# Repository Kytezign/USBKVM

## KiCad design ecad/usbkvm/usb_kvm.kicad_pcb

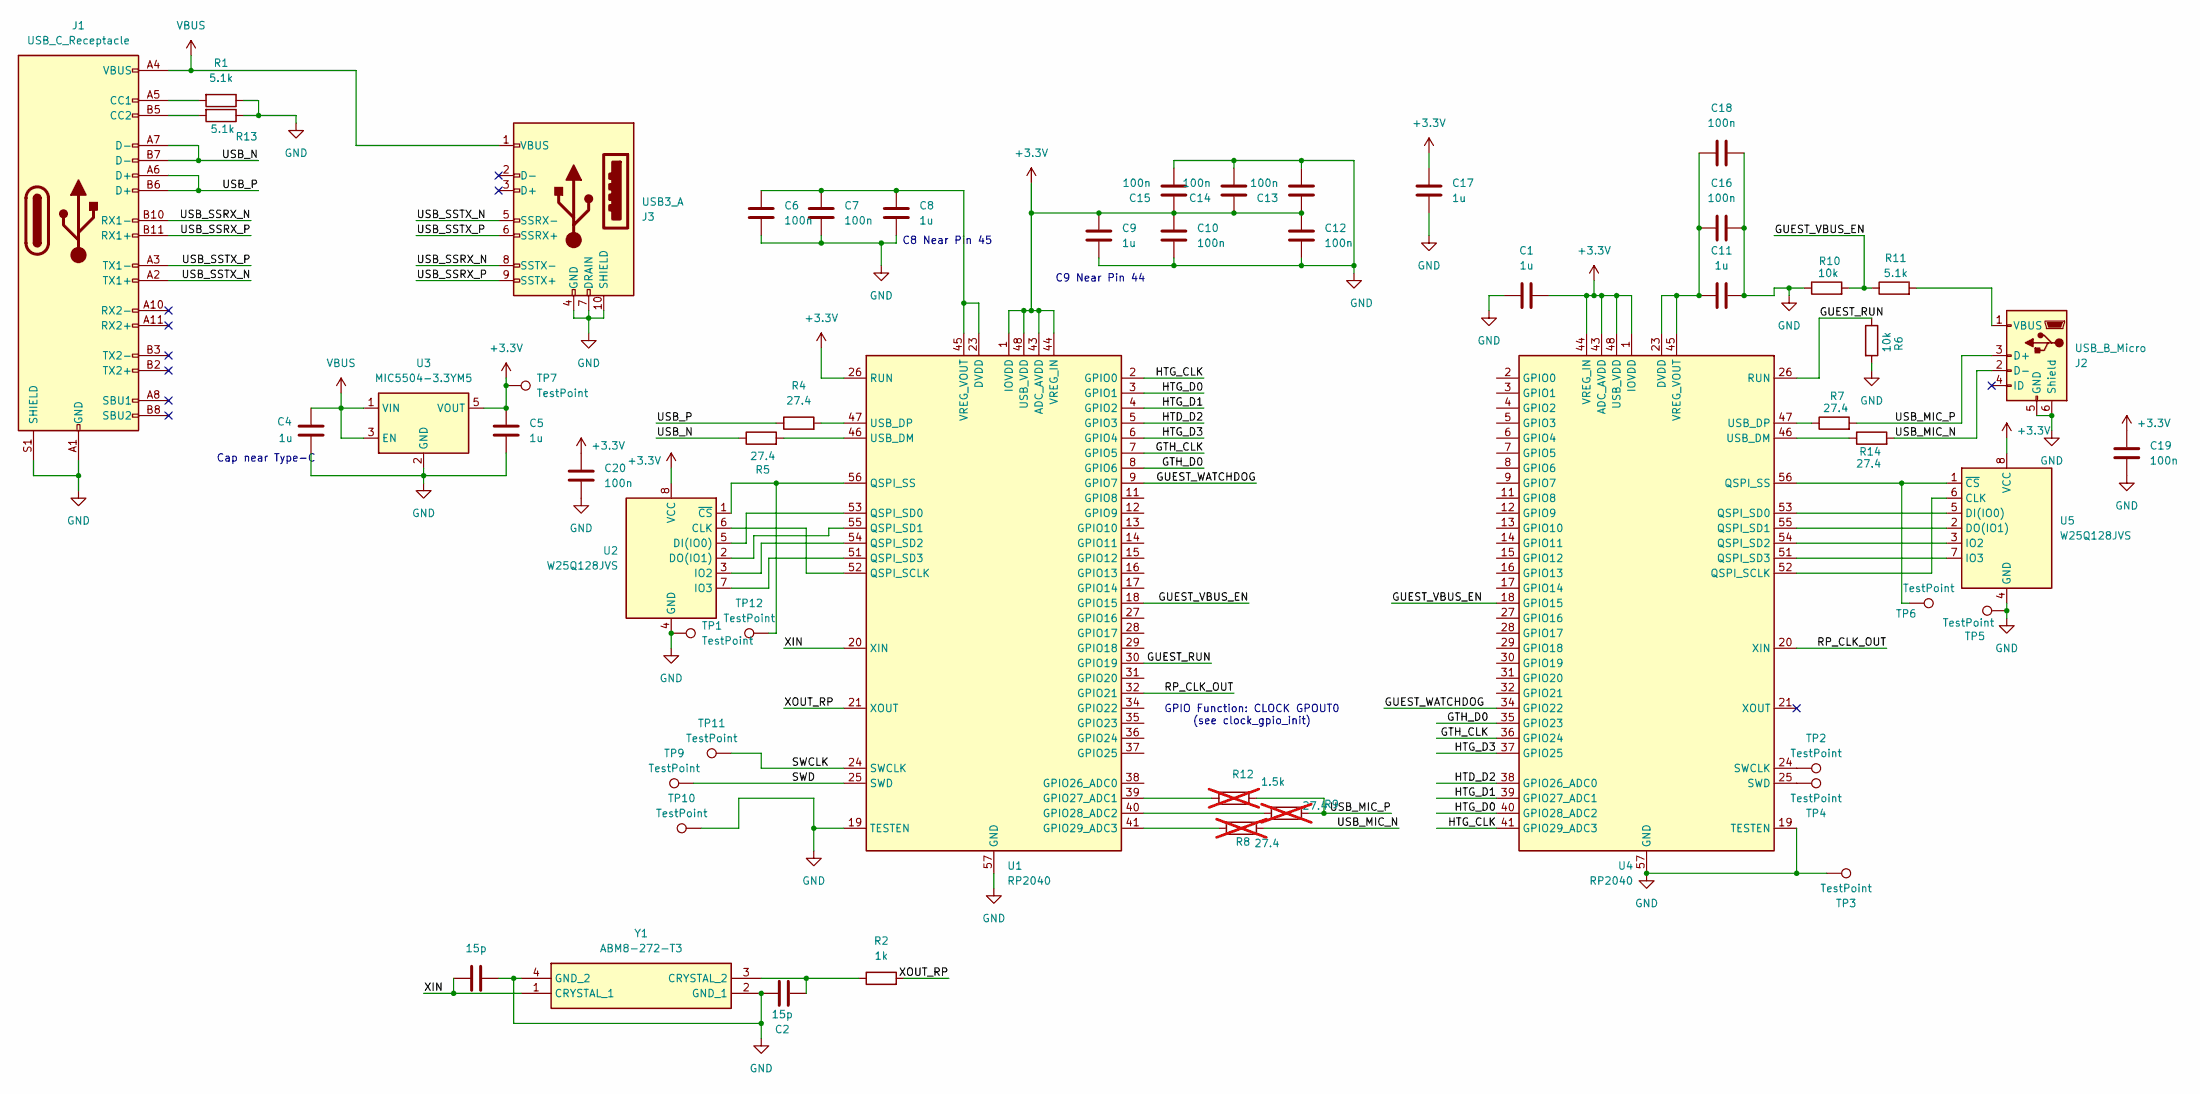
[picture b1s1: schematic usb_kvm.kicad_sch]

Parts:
C1, C4, C5, C8, C9, C11, C17: 1u; C_0402_1005Metric_Pad0.74x0.62mm_HandSolder
C2, C3: 15p; C_0402_1005Metric_Pad0.74x0.62mm_HandSolder
C6, C7, C10, C12, C13, C14, C15, C16, C18, C19, C20: 100n; C_0402_1005Metric_Pad0.74x0.62mm_HandSolder
J1: USB_C_Receptacle; USB405603A
J2: USB_B_Micro; 101181920001LF
J3: USB3_A; USBA3SRA
R1, R11, R13: 5.1k; R_0402_1005Metric_Pad0.72x0.64mm_HandSolder
R2: 1k; R_0402_1005Metric_Pad0.72x0.64mm_HandSolder
R4, R5, R7, R14: 27.4; R_0402_1005Metric_Pad0.72x0.64mm_HandSolder
R6, R10: 10k; R_0402_1005Metric_Pad0.72x0.64mm_HandSolder
R8, R9: 27.4; R_0402_1005Metric_Pad0.72x0.64mm_HandSolder; not fitted
R12: 1.5k; R_0402_1005Metric_Pad0.72x0.64mm_HandSolder; not fitted
TP1, TP5, TP6, TP7, TP12: TestPoint; TestPoint_THTPad_D1.0mm_Drill0.5mm
TP2, TP3, TP4, TP9, TP10, TP11: TestPoint; TestPoint_Pad_1.5x1.5mm
U1, U4: RP2040; QFN-56-1EP_7x7mm_P0.4mm_EP3.2x3.2mm
U2, U5: W25Q128JVS; SOIC-8_5.23x5.23mm_P1.27mm
U3: MIC5504-3.3YM5; SOT-23-5
Y1: ABM8-272-T3; ABM8272T3; Mouser Part Number 815-ABM8-272-T3

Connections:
+3.3V: C1.2, C5.1, C9.1, C10.1, C12.1, C13.1, C14.1, C15.1, C17.1, C19.1, C20.1, TP7.1, U1.1 (IOVDD), U1.10 (IOVDD), U1.22 (IOVDD), U1.26 (RUN), U1.33 (IOVDD), U1.42 (IOVDD), U1.43 (ADC_AVDD), U1.44 (VREG_IN), U1.48 (USB_VDD), U1.49 (IOVDD), U2.8 (VCC), U3.5 (VOUT), U4.1 (IOVDD), U4.10 (IOVDD), U4.22 (IOVDD), U4.33 (IOVDD), U4.42 (IOVDD), U4.43 (ADC_AVDD), U4.44 (VREG_IN), U4.48 (USB_VDD), U4.49 (IOVDD), U5.8 (VCC)
/GTH_CLK: U1.7 (GPIO5), U4.36 (GPIO24)
/GTH_D0: U1.8 (GPIO6), U4.35 (GPIO23)
/GUEST_RUN: R6.1, U1.30 (GPIO19), U4.26 (RUN)
/GUEST_VBUS_EN: R10.2, R11.1, U1.18 (GPIO15), U4.18 (GPIO15)
/GUEST_WATCHDOG: U1.9 (GPIO7), U4.34 (GPIO22)
/HTD_D2: U1.5 (GPIO3), U4.38 (GPIO26_ADC0)
/HTG_CLK: U1.2 (GPIO0), U4.41 (GPIO29_ADC3)
/HTG_D0: U1.3 (GPIO1), U4.40 (GPIO28_ADC2)
/HTG_D1: U1.4 (GPIO2), U4.39 (GPIO27_ADC1)
/HTG_D3: U1.6 (GPIO4), U4.37 (GPIO25)
/RP_CLK_OUT: U1.32 (GPIO21), U4.20 (XIN)
/SWCLK: TP11.1, U1.24 (SWCLK)
/SWD: TP9.1, U1.25 (SWD)
/USB_MIC_N: J2.2 (D-), R8.1, R14.2
/USB_MIC_P: J2.3 (D+), R7.2, R9.2, R12.2
/USB_N: J1.A7 (D-), J1.B7 (D-), R5.1
/USB_P: J1.A6 (D+), J1.B6 (D+), R4.1
/USB_SSRX_N: J1.B10 (RX1-), J3.8 (SSTX-)
/USB_SSRX_P: J1.B11 (RX1+), J3.9 (SSTX+)
/USB_SSTX_N: J1.A2 (TX1+), J3.5 (SSRX-)
/USB_SSTX_P: J1.A3 (TX1-), J3.6 (SSRX+)
/XIN: C3.1, U1.20 (XIN), Y1.1 (CRYSTAL_1)
/XOUT_RP: R2.2, U1.21 (XOUT)
GND: C1.1, C2.1, C3.2, C4.2, C5.2, C6.2, C7.2, C8.2, C9.2, C10.2, C11.2, C12.2, C13.2, C14.2, C15.2, C16.2, C17.2, C18.2, C19.2, C20.2, J1.A1 (GND), J1.A12 (GND), J1.B1 (GND), J1.B12 (GND), J1.MH3, J1.S1 (SHIELD), J2.5 (GND), J2.6 (Shield), J3.4 (GND), J3.7 (DRAIN), J3.10 (SHIELD), R1.1, R6.2, R10.1, R13.1, TP1.1, TP3.1, TP5.1, TP10.1, U1.19 (TESTEN), U1.57 (GND), U2.4 (GND), U3.2 (GND), U4.19 (TESTEN), U4.57 (GND), U5.4 (GND), Y1.2 (GND_1), Y1.4 (GND_2)
unnamed: J1.A5 (CC1), R1.2
unnamed: J1.B5 (CC2), R13.2
unnamed: J2.1 (VBUS), R11.2
unnamed: R12.1, U1.39 (GPIO27_ADC1)
unnamed: R9.1, U1.40 (GPIO28_ADC2)
unnamed: R8.2, U1.41 (GPIO29_ADC3)
unnamed: U1.52 (QSPI_SCLK), U2.6 (CLK)
unnamed: U1.53 (QSPI_SD0), U2.5 (DI(IO0))
unnamed: U1.55 (QSPI_SD1), U2.2 (DO(IO1))
unnamed: U1.54 (QSPI_SD2), U2.3 (IO2)
unnamed: U1.51 (QSPI_SD3), U2.7 (IO3)
unnamed: TP12.1, U1.56 (QSPI_SS), U2.1 (~CS)
unnamed: R5.2, U1.46 (USB_DM)
unnamed: R4.2, U1.47 (USB_DP)
unnamed: C6.1, C7.1, C8.1, U1.23 (DVDD), U1.45 (VREG_VOUT), U1.50 (DVDD)
unnamed: U4.52 (QSPI_SCLK), U5.6 (CLK)
unnamed: U4.53 (QSPI_SD0), U5.5 (DI(IO0))
unnamed: U4.55 (QSPI_SD1), U5.2 (DO(IO1))
unnamed: U4.54 (QSPI_SD2), U5.3 (IO2)
unnamed: U4.51 (QSPI_SD3), U5.7 (IO3)
unnamed: TP6.1, U4.56 (QSPI_SS), U5.1 (~CS)
unnamed: TP2.1, U4.24 (SWCLK)
unnamed: TP4.1, U4.25 (SWD)
unnamed: R14.1, U4.46 (USB_DM)
unnamed: R7.1, U4.47 (USB_DP)
unnamed: C11.1, C16.1, C18.1, U4.23 (DVDD), U4.45 (VREG_VOUT), U4.50 (DVDD)
unnamed: C2.2, R2.1, Y1.3 (CRYSTAL_2)
VBUS: C4.1, J1.A4 (VBUS), J1.A9 (VBUS), J1.B4 (VBUS), J1.B9 (VBUS), J3.1 (VBUS), U3.1 (VIN), U3.3 (EN)

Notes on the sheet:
C9 Near Pin 44
GPIO Function: CLOCK GPOUT0 (see clock_gpio_init)
Cap near Type-C
C8 Near Pin 45

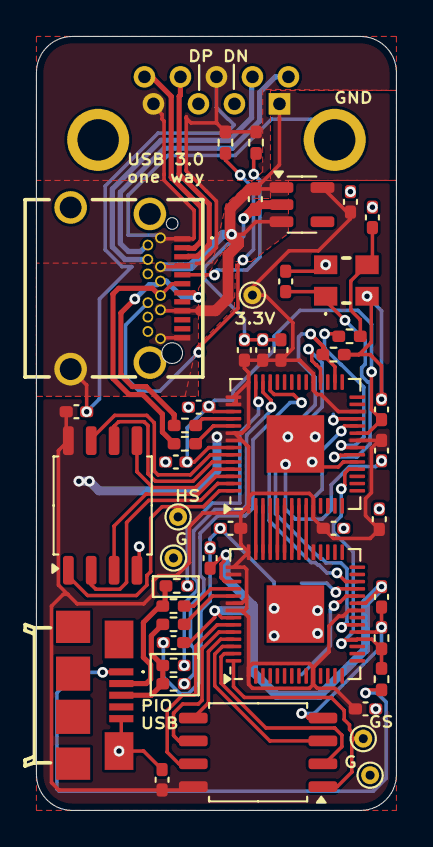
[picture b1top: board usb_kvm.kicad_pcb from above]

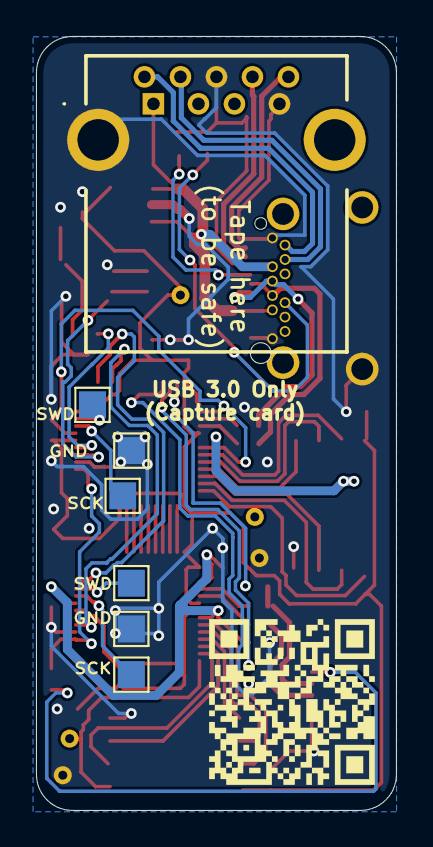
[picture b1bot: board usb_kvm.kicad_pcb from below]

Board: 2 copper layers, 20.0 x 43.0 mm, 53 parts (7 on the bottom side), 53 nets.

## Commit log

2024-09-27 Readme Cleanup - also testing github flow
2024-09-27 Added Example Pictures (and maybe a tag?)
2024-09-28 License
2024-11-09 Added ZIG/SDL3 based GUI option.
    Documentation Cleanup
2025-02-08 Good enough to release.
2025-02-08 Added pictures
2025-02-08 2nd try with pictures
